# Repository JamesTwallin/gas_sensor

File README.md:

# Atmospheric methane detector

A pocket-sized gas detector you carry on a walk to find methane leaks.

- A small circuit board holds two gas sensors, one for methane and one for LP
  gas (propane and butane).
- The board sends its readings to an app on your phone over Bluetooth.
- The app shows you when the gas level suddenly rises, and saves the readings
  together with your GPS position.
- Afterwards, scripts in this repository turn a recording into a map.

This is a home-built, citizen-science project. It is not a certified safety
device. It shows *where* gas rises; it does not tell you how much gas there is.

## The board

There is one board: [hardware/board](hardware/board/), 66 × 36 mm. It has been
made by JLCPCB and works (October 2026). Order it with the files in
[hardware/board/production](hardware/board/production/).

The **air blade** is a tiny plug-in board that measures airflow and the outside
air's temperature and humidity. It is not ready to order: the way it attaches to
the board is being redesigned. The board works without it.

[hardware/board_mems](hardware/board_mems/) is a test version of the board with a
second plug-in for two cheap MEMS gas sensors, to compare them with the Figaro
sensors. It has not been made.

Older designs (the first prototype, earlier boards and cases) are in
[archive/](archive/), for reference only.

## What you need

| Item | Where to get it | Notes |
|---|---|---|
| The circuit board | Order from [JLCPCB](https://jlcpcb.com/) using the files in [hardware/board/production](hardware/board/production/). | It arrives with almost every part already soldered on. The [board guide](hardware/board/README.md) lists which options to pick when ordering. |
| Methane sensor: Figaro **TGS2611-E00** | [RS Components, stock no. 134-6647](https://uk.rs-online.com/web/p/environmental-sensor-ics/1346647) | You solder this on yourself. It has four legs. |
| LP-gas sensor: Figaro **TGS2610-D00** | RS Components, stock no. 134-6641 (search for it on your country's RS site) | You solder this on yourself too. |
| Battery | EEMB 103454RP, 2000 mAh 3.7 V LiPo with a JST-PH plug (Amazon, eBay or EEMB's own shop) | **Check the red and black wires before plugging it in**, see below. It is the size the case is made for; any single-cell 3.7 V LiPo with a JST-PH plug and built-in protection works outside the case. |
| USB-C cable | Any | For charging the battery and loading the software. |
| Android phone | | For the app. An iPhone works only if you build the app yourself. |
| Case (optional) | 3D-print it from [hardware/enclosure](hardware/enclosure/) | Also needs four M2 × 8 mm and two M2 × 5 mm self-tapping screws. |

The two sensors together cost roughly $25–30. Not every electronics shop stocks
them, so use the part names above when searching.

**Battery wires.** Batteries with the same plug are not all wired the same way
round. Some come with red and black swapped compared to what this board
expects, and the two metal pins have to be swapped over in the plug. A battery plugged in the wrong way round does no damage, but the board
will not switch on. The [board guide](hardware/board/README.md#before-you-power-it)
shows which side is positive.

## Putting it together

1. **Order the board** from JLCPCB.
2. **Solder on the two sensors.** Line up the small tab on each sensor with the
   notch printed on the board.
3. **Load the software onto the board.** Install
   [PlatformIO](https://platformio.org/), plug the board into your computer with
   the USB-C cable, **switch the board on** (with the switch off, the computer
   cannot see the board at all, even on USB), and run these from this folder:

   ```
   pio run -d firmware/phone_board                    # build
   pio run -d firmware/phone_board --target upload    # load it onto the board
   ```

   A new board arrives empty and will not show up properly until it has been
   loaded once: hold the **BOOT** button, tap **RESET**, let go of **BOOT**, and
   run the upload again. Press **RESET** afterwards to start it. Use a USB cable
   that carries data; some only charge.
4. **Install the app.** On an Android phone, scan this code, or open the
   [direct link](https://expo.dev/artifacts/eas/GfUwoBCFfugQeaA97EXnztzByZKVXR2_-AvwwxxLo4k.apk)
   on the phone. Your phone will ask for permission to install it.

   This is the version built on 2 October 2026. The download is stored by Expo
   and will be removed after a while. If the code has stopped working, or you
   have an iPhone, build the app yourself: see the [app guide](app/README.md).
   The app has a pretend sensor built in, so you can try it before you have a
   board.
5. **Plug in the battery**, after checking the wires (above). Plugging in the
   USB-C cable charges it.
6. **Go for a walk.** Switch the board on, open the app, tap **Connect**, pick
   your board from the list, and tap **Record**.

A quick way to check it works: let a little gas out of an unlit cigarette
lighter near the sensors, for a second or two only. The LP-gas reading should
jump. The methane reading will not, because that sensor has a filter that blocks
lighter gas.

## How it finds gas

The sensors do not give a steady number. Their readings drift up and down with
the temperature, the humidity and the wind, even in clean air. So the app does
not look at how high the reading is. It looks at how fast the reading is
*changing*. Walking into a patch of gas makes the reading shoot up within a
second or two, and the app flags that moment.

For the same reason, the gas concentration the app shows (in parts per million)
is only a rough guide.

More detail, for those who want it:

- [docs/phone_board.md](docs/phone_board.md): how the board is designed and
  how it talks to the phone.
- [docs/sensors.md](docs/sensors.md): how the sensors behave, and what can
  fool them.
- [app/README.md](app/README.md): the app.

## Making a map from a recording

The app saves each walk as a spreadsheet-style file (a CSV). Share it from the
app's **Surveys** tab to your computer and put it in the `tools/data/` folder.
Then, with [Python](https://www.python.org/) installed:

```
pip install -r tools/requirements.txt   # once
python tools/plot_map.py                # makes a map for every recording
python tools/plot_survey.py             # makes a video for every recording
```

- [plot_map.py](tools/plot_map.py) draws your route on a satellite photo,
  coloured by the sensor reading. The maps appear in `tools/maps/`.
- [plot_survey.py](tools/plot_survey.py) makes a video of the readings over
  time. The videos appear in `tools/videos/`.

Recordings contain your GPS positions, so `tools/data/` is never uploaded to
GitHub.

## What is in this repository

```
app/              the phone app
firmware/         the software that runs on the board
hardware/
  board/          the board: design files and the files to order it
  board_mems/     the MEMS sensor test version of the board (not made)
  air_blade/      the airflow plug-in (being redesigned)
  mems_blade/     the MEMS sensor plug-in for board_mems (not made)
  enclosure/      the 3D-printed case
docs/             how the board and the sensors work
tools/            scripts that turn recordings into maps and videos
archive/          old versions, kept for reference
```

## Licence

Firmware is MIT (see [LICENSE](LICENSE)). The hardware design will be released
under CERN-OHL-S once it is ready.

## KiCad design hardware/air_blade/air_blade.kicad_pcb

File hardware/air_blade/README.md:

# Air blade

A tiny plug-in board for the [phone-companion board](../board/).
It stands upright in a notch in the board's sensor end, between the two gas sensor
cans, and pokes 4.5 mm out through a slot in the case face, so its tip sits in the
outside air level with the gas sensors' caps. It carries:

- **an outside-air temperature/humidity sensor** (SHT40-CD1B, I²C address 0x46;
  an SHT40-BD1B at 0x45 works too, but never an -AD1B, which clashes with the
  board's own). The board's own SHT40 (0x44) sits inside the case and reads the
  case air, warmed by the gas sensors' heaters; this one reads the street;
- **the heated airflow thermistor** (a 1 kΩ NTC). Moving air cools it; the
  firmware turns that into an airflow index for the gas detector
  ([docs/HARDWARE.md](../../docs/HARDWARE.md) section 1). The SHT40 beside it gives
  it the air temperature it needs.

## Status: being redesigned, do not order

**The design in this folder can't realistically be fitted, so don't order it.**
The board's blade pads (J3) sit in a 3.8 mm gap between the two sensor cans, which
stand 13 mm tall, and they stop 0.3 mm short of the notch the blade stands in. So
the blade never touches them, and every joint has to be made down in that narrow
gap, where a soldering iron can't realistically reach. The design itself passes
KiCad's checks; the problem is getting it onto the board.

A new design is being worked out. The options so far:

- **for boards already made:** solder short flying wires flat onto J3 first, while
  there is still room, and move the blade's joints higher up, where an iron can reach;
- **for future boards:** a proper slot through the board with pads on the
  underside, so the blade can be soldered from below.

**The first batch is unusable.** It was drawn mirror-image: its pads meet J3 in
reverse order, so its ground lands on the board's SCL and its SDA on the thermistor
feed. Soldered in, it holds the board's I²C bus at about 0.5–1 V and nothing on the
bus answers (seen on the bench 2026-10-22). Its flat foot pads also never touched
J3, so solder had to bridge the gap and bridged to the next pad instead. Never
solder one of those blades (flat pads, no holes) to J3. Their files are in
[archive/air_blade_first_batch](../../archive/air_blade_first_batch/).

The design here fixes the mirror error and the pads. It:

- is **the right way round**: seen from the parts side, the thermistor prong is on
  the left, over J3 pad 1 by the CH4 can, and the SHT40 on the right. That also puts
  each part over its own pocket in the case guide;
- has **five plated holes** instead of flat pads. A short leg of 0.5 mm wire goes
  through each one and bends down onto its J3 pad. A plated hole runs right through
  the board, so it cannot peel off like a flat pad;
- has the holes in **two staggered rows**, so neighbouring joints are 2 mm apart,
  not 1 mm;
- has **wider tracks** (0.25 mm) from below the prongs down to the foot;
- is drawn at **1.6 mm** thick, which is what the case is set up for;
- relies on the case guide and a bead of epoxy to hold it, not the solder.

The pin table, parts and shape below still hold for the redesign unless it says
otherwise.

## Shape

5.7 × 14.9 mm, 2 layers, **1.6 mm thick**.

- **Tip: two prongs, 1 mm apart.** The SHT40 and its capacitor are on one, the
  heated thermistor on the other, so the thermistor's warmth (2.7 mW) does not
  reach the SHT40. The gap runs down to just below the case face.
- **Foot:** five plated holes for wire legs, just above two small shoulders. The
  shoulders rest on the board's top surface; below them a tab drops into its notch.
- **No copper pours,** and thin (0.15 mm) tracks on the prongs: copper would carry
  the thermistor's heat away and blunt the airflow signal. Lower down, inside the
  case, the tracks are 0.25 mm.

| Foot hole | Net | Board's J3 pad |
|---|---|---|
| 1 | heated thermistor | 1 |
| 2 | GND | 2 |
| 3 | 3.3 V | 3 |
| 4 | SCL | 4 |
| 5 | SDA | 5 |

## Parts

All three are assembled by JLC (LCSC numbers in `production/bom.csv`):

| Ref | Part | LCSC | What it does |
|---|---|---|---|
| U1 | Sensirion SHT40-CD1B-R3 | C7461852 | outside-air temperature and humidity, I²C 0x46 |
| C1 | 100 nF 0402 | C1525 | U1's supply decoupling |
| RT1 | Murata NCP18XQ102J03RB, 1 kΩ NTC, 0603, B 3650 K | C152577 | heated airflow thermistor, fed 2.7 mW through the board's R28 (1 kΩ) |

## Ordering from JLCPCB (not until the redesign)

**Don't follow these steps yet.** The current design can't be fitted (see
[Status](#status-being-redesigned-do-not-order)). They are kept for when the
redesign is ready.

The blade is too small for JLC to assemble on its own, and JLC's own panel
option ("Panel by JLCPCB") only does V-cut, which can't follow the forked tip
or the shoulders. So order the ready-made panel in **`production/panel/`**: 6
blades in a 35 × 46 mm frame, with tooling holes and alignment marks for the
assembly machine.

1. **PCB:** upload `production/panel/gerbers.zip`. 2 layers, **1.6 mm** thick.
   Leave **Delivery Format at "Single PCB"**: the file already is the panel, so
   the quantity counts panels (minimum 5 = 30 blades of bare board). 0.15 mm
   track and clearance, 0.45 mm vias with a 0.2 mm drill. Two of the vias sit in
   C1's pads: choose JLC's filled and capped via-in-pad option, as for the board.
2. **Assembly:** top side only, `production/panel/bom.csv` and
   `production/panel/cpl.csv`. Assemble **2 panels** (JLC's minimum) = 12 blades.
   Look over JLC's placement preview, especially each U1's pin-1 corner
   (positions matched to LCSC's footprints by `gen/jlc_align.py`).
3. **Breaking out:** each blade hangs on two small tabs of drilled holes on its
   long sides, below the fork. Bend each blade out with pliers, then file the
   two nubs flush so the blade slides through the case slot. The tips, the
   slot and the foot have no tabs, so they need no filing.

`production/gerbers.zip`, `bom.csv` and `cpl.csv` (one blade) are kept for reference.

## Fitting it to the board (for the current design)

These steps were written for the current design. On a real board, step 5 can't
realistically be done (see [Status](#status-being-redesigned-do-not-order)); they
are kept until the redesign replaces them.

You need: five pieces of **0.5 mm (24 AWG) solid tinned copper wire**, about 6 mm
long (offcuts of resistor legs work if they slide into the holes), flux, a fine
soldering tip, and quick-set epoxy.

1. **Legs into the blade.** Push one wire through each of the five foot holes from
   the back (the side with the "AIR BLADE B" label) so about 3 mm sticks out of the
   front (the side with the parts). Solder each one on the front, then trim the back
   flush and touch it with the iron so it is smooth. The case has only about 1 mm of
   room behind the blade.
2. **Bend the legs down.** Bend each leg down towards the tab, at a slant, so its end
   will rest on its J3 pad about 0.8 mm in front of the blade. The top row (holes 2
   and 4) bends a little steeper than the bottom row (1, 3 and 5).
3. **Tin the board's J3 pads,** the five pads beside the notch between the cans, labelled
   BLADE.
4. **Stand the blade in the notch,** parts facing the middle of the board, with the
   shoulders flat on the board. Seen from the middle of the board, the thermistor prong
   is on the left, on the CH4 can's side. Each leg should land on its own J3 pad:
   hole 1 (bottom left) on pad 1, the one nearest the CH4 can. Trim any leg that reaches past its pad.
5. **Solder each leg to its pad.** Check that no two pads are joined, then check each
   of the five connections with a meter. Before fitting the case, power the board
   on USB: the serial log should say "Air blade SHT40 found at 0x46".
6. **Epoxy.** Run a small bead of epoxy along both shoulders where they sit on the
   board, and into the notch around the tab. Keep it off the prongs. This bead, not
   the solder, is what holds the blade upright. Let it set before you fit the case.
7. **Fit the board into the front shell**
   ([hardware/enclosure](../enclosure/), `stl/front.stl`) straight down,
   not tilted: the blade slides into a guide on the inside of the face and out
   through the slot between the sensor collars. The guide holds it over 5.8 mm, so
   knocks on the tip go into the case, not the joints.

**First-batch blades** (flat pads, no holes) are wired in reverse and must not be
soldered to J3: they stop the board's I²C bus working.

## Firmware

Nothing to set: the board's firmware (`pio run -d firmware/phone_board -e
board`) looks for an SHT40 at 0x45, then 0x46, at start-up. When it finds one, that
supplies the temperature and humidity (to the phone and to the gas detector), the
on-board SHT40 is logged as `case_temp_c` / `case_rh_pct` on USB serial, and the
Info JSON says `"t_src":2`. Then run the still-air calibration
([docs/HARDWARE.md](../../docs/HARDWARE.md) section 1.6).

## The design is generated

As for the board: edit `gen/design.py`, then

| Step | Command |
|---|---|
| schematic | `python gen/build_sch.py` |
| board (placed and routed: every track is in `design.py`) | `"C:\Program Files\KiCad\9.0\bin\python.exe" gen/build_pcb.py` |
| JLC placement | `...\python.exe gen/jlc_align.py` |
| fab files + renders | `python gen/export.py` |
| 6-up panel for ordering (needs `pip install kikit` in KiCad's python) | `...\python.exe gen/build_panel.py` |

Checks: `kicad-cli pcb drc --schematic-parity air_blade.kicad_pcb` and `kicad-cli sch
erc air_blade.kicad_sch`. Last run (2026-10-22): 0 violations, 0 unconnected, 0
parity issues; ERC 0 errors, 0 warnings.

## Not known yet

- How much the thermistor self-heats on the blade (an estimate is about 1 °C:
  some of its heat goes into the blade, not the air), and how strongly its
  reading follows airflow. The still-air calibration and the airflow survey in
  [docs/PROTOCOL.md](../../docs/PROTOCOL.md) measure both.
- Which way the redesign goes (see [Status](#status-being-redesigned-do-not-order)).
  The slot geometry in the case is tied to this design and will change with it.

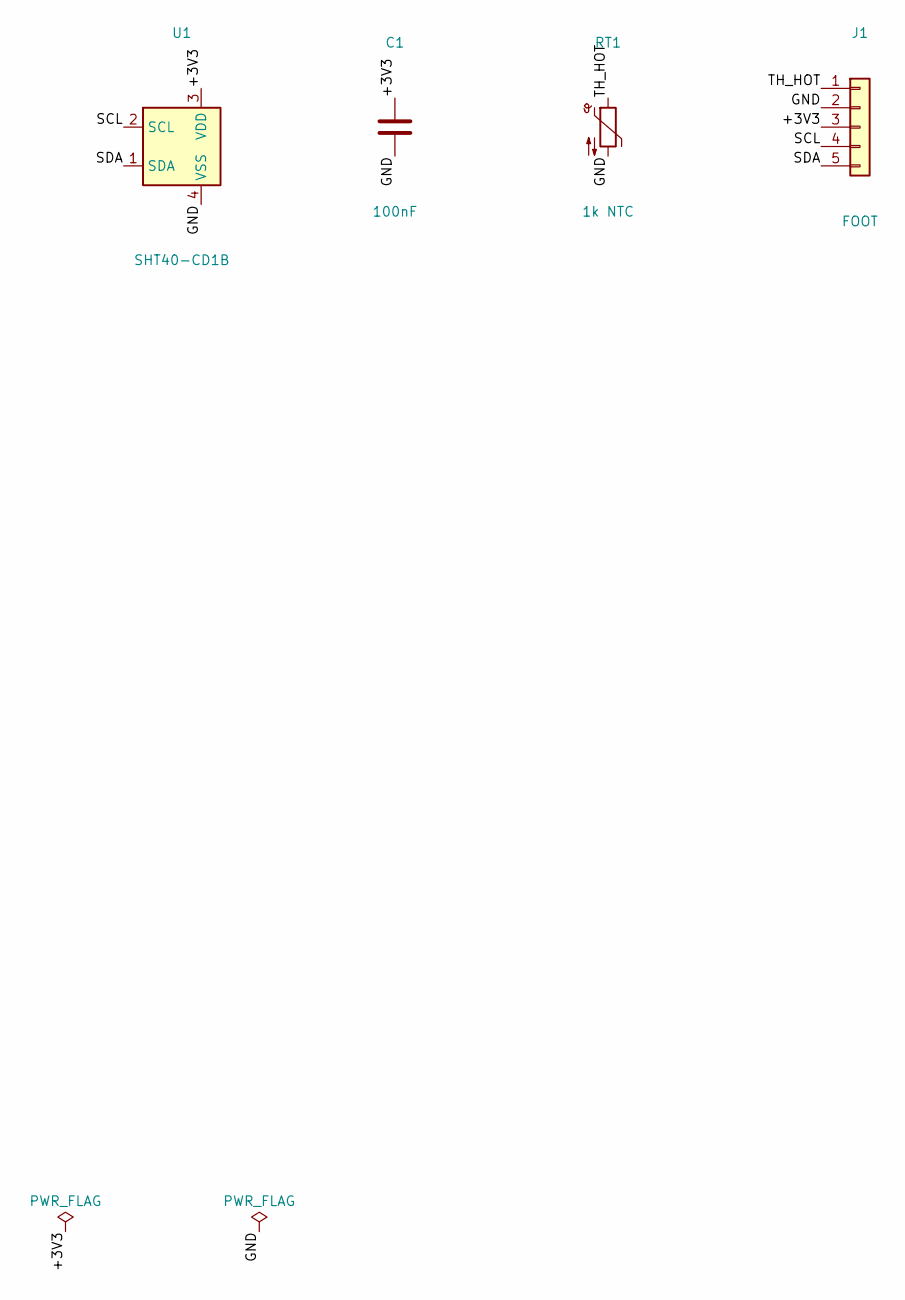
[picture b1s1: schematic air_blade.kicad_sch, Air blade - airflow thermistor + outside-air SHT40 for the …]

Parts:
C1: 100nF; C_0402_1005Metric; LCSC C1525
J1: FOOT; BladeFoot_1x05_Legs
RT1: 1k NTC; R_0603_1608Metric; MPN NCP18XQ102J03RB; LCSC C152577
U1: SHT40-CD1B; Sensirion_DFN-4_1.5x1.5mm_P0.8mm_SHT4x_NoCentralPad; MPN SHT40-CD1B-R3; LCSC C7461852

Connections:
/+3V3: C1.1, J1.3, U1.3 (VDD)
/GND: C1.2, J1.2, RT1.2, U1.4 (VSS)
/SCL: J1.4, U1.2 (SCL)
/SDA: J1.5, U1.1 (SDA)
/TH_HOT: J1.1, RT1.1

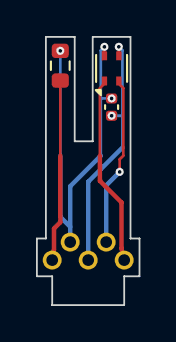
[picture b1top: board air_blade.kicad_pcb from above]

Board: 2 copper layers, 5.7 x 14.9 mm, 4 parts (0 on the bottom side), 5 nets.

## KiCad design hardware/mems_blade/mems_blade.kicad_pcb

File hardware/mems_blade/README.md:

# MEMS blade (for the MEMS rig)

A small plug-in board, 11.4 x 18.4 mm and 1.6 mm thick, that carries two MEMS gas
sensors for the [MEMS rig](../board_mems/)'s sensor comparison
([docs/mems_rig.md](../../docs/mems_rig.md)). It stands upright in a notch in the rig's
sensor end, beside the LPG sensor, and its tip stands 8 mm out of a slot in the case
face, so both sensors breathe the same air as the Figaro sensors and the air blade.

**Status: designed, not built. Redrawn on 2026-10-22 and not yet tried against a
real board.** The first drawing was a mirror image of what J5 needs (the same mistake
as the first batch of air blades), so its pads would have missed J5. It has been
redrawn with the parts the right way round (see "Why it was redrawn" below). Check the
pin order against J5 once more before ordering.

## What is on it

| Ref | Part | LCSC | What it does |
|---|---|---|---|
| U1 | Saiya **SY-CH4-37BPM**, 3.8 x 3.8 mm | C22363924 | methane sensor (sensor A, `mems_a`) |
| R1 | 82 ohm, 0603 | C23255 | U1's heater resistor: 5 V in, about 3.6 V and 60 mW at the heater |
| R3, R4 | 10 k + 10 k, 0402 | C25744 | U1's load (20 k), read at the middle |
| U2 | SGX **MiCS-5524**, 5 x 7 mm | C3659348 | CO, hydrogen and other reducing gases, weak on methane (sensor B, `mems_b`) |
| R2 | 82 ohm, 0805 | C17841 | U2's heater resistor: about 2.4 V and 76 mW at the heater; it drops 84 mW itself, hence 0805 |
| R5, R6 | 100 k + 100 k, 0402 | C25741 | U2's load (200 k), read at the middle |
| C1 | 1 uF | C52923 | heater feed decoupling |
| C2 | 100 nF | C1525 | 3.3 V decoupling |
| J1 | 5 plated foot holes for wire legs | (not assembled) | wire legs to the rig's J5 |

Foot holes, from the one nearest the LPG can: 1 sensor A output, 2 GND, 3 3.3 V,
4 switched 5 V for the heaters, 5 sensor B output.

The parts face the case's end wall, not the middle of the board: facing the middle,
the sensors would hit the case's H1 screw boss on the way into the shell. The foot
pads are on the back. The heater resistors and the load resistors sit low on the
blade, inside the case, so their warmth stays away from the sensors.

## Ordering from JLCPCB

The blade is below JLC's minimum size for assembly, so order the ready-made panel in
**`production/panel/`**: 6 blades in a 52 x 53 mm frame, with tooling holes and
fiducials.

1. **PCB:** upload `production/panel/gerbers.zip`. 2 layers, **1.6 mm**. Leave
   Delivery Format at "Single PCB" (the file already is the panel), so the quantity
   counts panels.
2. **Assembly:** top side only, `production/panel/bom.csv` and
   `production/panel/cpl.csv`. Assemble **2 panels** (JLC's minimum) = 12 blades.
   Positions are already matched to LCSC's footprints (`gen/jlc_align.py`). Check the
   preview, especially both sensors' orientation.
3. **Reserve the sensors first.** LCSC had only 71 SY-CH4-37BPM in stock on
   19 October 2026. Add them to your JLC parts library before ordering.
4. **Breaking out:** each blade hangs on one small tab of drilled holes on each long
   side, about level with the case face. Bend the blade out, then **file both nubs
   flush**, or they catch in the case slot.

`production/gerbers.zip`, `bom.csv` and `cpl.csv` (one blade) are kept for reference.

## Fitting it to the MEMS rig

You need five pieces of **0.5 mm (24 AWG) solid tinned copper wire**, about 6 mm long,
flux, a fine tip and quick-set epoxy, as for the [air blade](../air_blade/README.md).

1. **Legs into the blade.** Push a wire through each foot hole from the parts side so
   about 3 mm sticks out of the back (the side with the "MEMS BLADE A" label). Solder
   each one, then trim the parts side flush.
2. **Bend the legs down** at a slant towards the tab, so each end will rest on its J5
   pad about 0.8 mm out from the blade's back.
3. **Tin the rig's J5 pads** (the five pads beside the second notch, labelled MEMS).
4. **Stand the blade in the notch** with the **sensors facing away from the middle of
   the board** (the legs towards J5) and the shoulders flat on the board. Seen from the
   end wall, the methane sensor (37BPM) is on the left and the MiCS-5524 on the right,
   over the LPG can's side. Hole 1 lands on J5 pad 1, the one nearest the LPG can.
5. **Solder each leg to its pad,** check no two pads are joined, and check each
   connection with a meter.
6. **Epoxy** a small bead along both shoulders and into the notch around the tab. That,
   not the solder, holds the blade up.
7. Fit the board into the MEMS rig's front shell
   (`hardware/enclosure/stl/front_mems.stl`) straight down: the blade goes out through
   the slot beside the LPG cap.
8. Bring the battery lead up past the **other** end corner (the power-switch side) and
   over the board to the battery plug: the blade now stands where the lead goes on the
   plain board.

### Why it was redrawn

Fixed on 2026-10-22, before any were made. The first drawing of this blade was a
mirror image, the same mistake as the first batch of air blades (soldered in, one of
those stopped the board's I2C bus). Its flat foot pads would also have missed J5 by
about 0.3 mm each way. It now has the parts the right way round and wire-leg holes
instead of flat pads.

## Before you survey

- **Burn in 48 hours** with the board running (the firmware counts the hours). The
  Saiya datasheet asks for at least 4 hours powered after soldering.
- **Warm up 60 minutes** after every power-up. The firmware ignores the MEMS readings
  until then.

## The design is generated: edit `gen/design.py`, not the KiCad files

As for the air blade. `gen/design.py` holds the parts, nets, LCSC numbers, outline
and placement; the scripts build the KiCad project from it.

| Step | Command (from this folder) |
|---|---|
| schematic | `python gen/build_sch.py` |
| board (placed) | `"C:\Program Files\KiCad\9.0\bin\python.exe" gen/build_pcb.py` |
| autoroute | `...\python.exe gen/route.py` (needs `JAVA` and `FREEROUTING`, as for the MEMS rig board) |
| JLC placement | `...\python.exe gen/jlc_align.py` (needs `EASYEDA2KICAD`) |
| fab files + renders | `python gen/export.py` |
| 6-up panel | `...\python.exe gen/build_panel.py` (needs `kikit` in KiCad's python) |

The two sensor footprints, symbols and 3D models came from LCSC through
easyeda2kicad (`lib/`). Their pins were checked against the datasheets: on the
37BPM, pads 1 and 5 are the heater and 3 and 7 the sensing electrodes; on the
MiCS-5524, C and F are the heater and D and G the sensing electrodes.

Checks: `kicad-cli pcb drc --schematic-parity mems_blade.kicad_pcb` and
`kicad-cli sch erc mems_blade.kicad_sch`. Last run (2026-10-22): **0 violations,
0 unconnected pads, 0 parity errors; ERC 0 errors, 0 warnings.**

## Not known yet

- Whether the redrawn blade lines up with J5 on a real board.
- Whether the load resistors (20 k, 200 k) put each sensor's clean-air output in a
  good range. Check once a blade runs: aim for roughly 100 to 800 mV at the tap.
- The MiCS-5524's response time, temperature and humidity behaviour, and burn-in.
- Whether wire legs plus epoxy hold a blade this size.

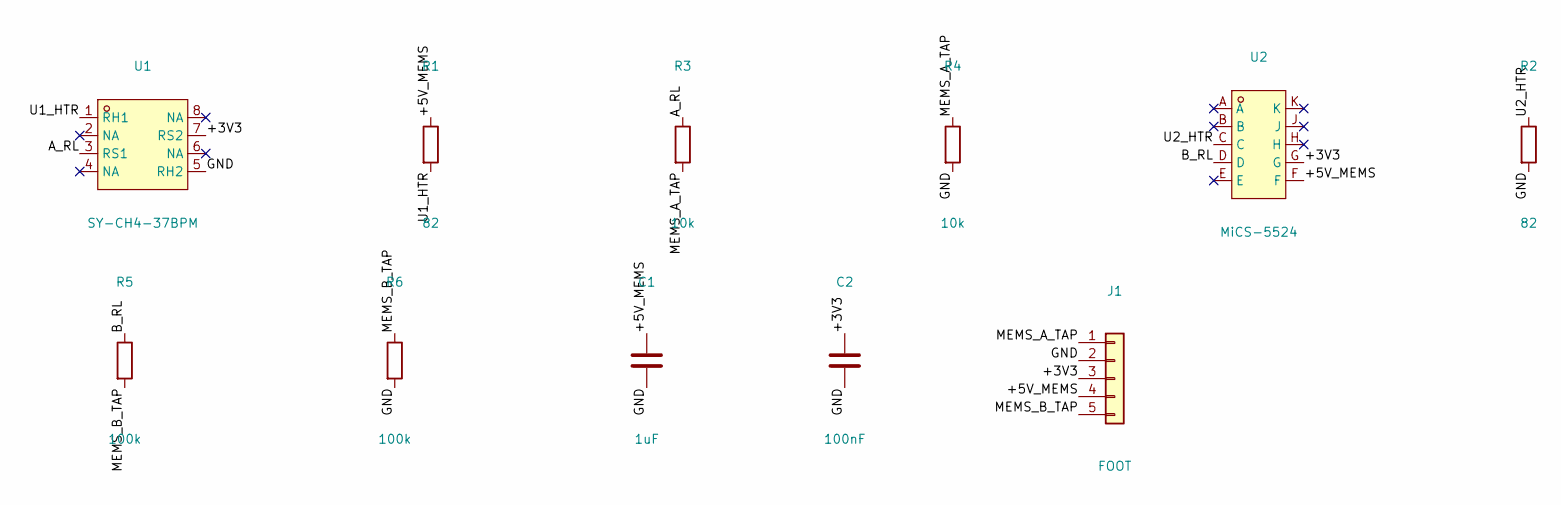
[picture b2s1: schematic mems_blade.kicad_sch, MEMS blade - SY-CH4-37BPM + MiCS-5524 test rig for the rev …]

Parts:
C1: 1uF; C_0402_1005Metric; LCSC C52923
C2: 100nF; C_0402_1005Metric; LCSC C1525
J1: FOOT; BladeFoot_1x05_Legs_P0.95mm
R1: 82; R_0603_1608Metric; LCSC C23255
R2: 82; R_0805_2012Metric; LCSC C17841
R3, R4: 10k; R_0402_1005Metric; LCSC C25744
R5, R6: 100k; R_0402_1005Metric; LCSC C25741
U1: SY-CH4-37BPM; MPN SY-CH4-37BPM; LCSC C22363924
U2: MiCS-5524; MICS-5524; MPN MICS-5524; LCSC C3659348

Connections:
/+3V3: C2.1, J1.3, U1.7 (RS2), U2.G
/+5V_MEMS: C1.1, J1.4, R1.1, U2.F
/A_RL: R3.1, U1.3 (RS1)
/B_RL: R5.1, U2.D
/GND: C1.2, C2.2, J1.2, R2.2, R4.2, R6.2, U1.5 (RH2)
/MEMS_A_TAP: J1.1, R3.2, R4.1
/MEMS_B_TAP: J1.5, R5.2, R6.1
/U1_HTR: R1.2, U1.1 (RH1)
/U2_HTR: R2.1, U2.C

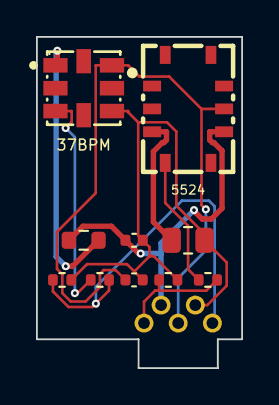
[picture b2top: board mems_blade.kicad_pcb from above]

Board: 2 copper layers, 11.4 x 18.4 mm, 11 parts (0 on the bottom side), 9 nets.

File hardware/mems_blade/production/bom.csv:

Comment,Designator,Footprint,LCSC Part #
1uF,C1,C_0402_1005Metric,C52923
100nF,C2,C_0402_1005Metric,C1525
82,R1,R_0603_1608Metric,C23255
82,R2,R_0805_2012Metric,C17841
10k,"R3,R4",R_0402_1005Metric,C25744
100k,"R5,R6",R_0402_1005Metric,C25741
SY-CH4-37BPM,U1,SY-CH4-37BPM,C22363924
MiCS-5524,U2,MICS-5524,C3659348
